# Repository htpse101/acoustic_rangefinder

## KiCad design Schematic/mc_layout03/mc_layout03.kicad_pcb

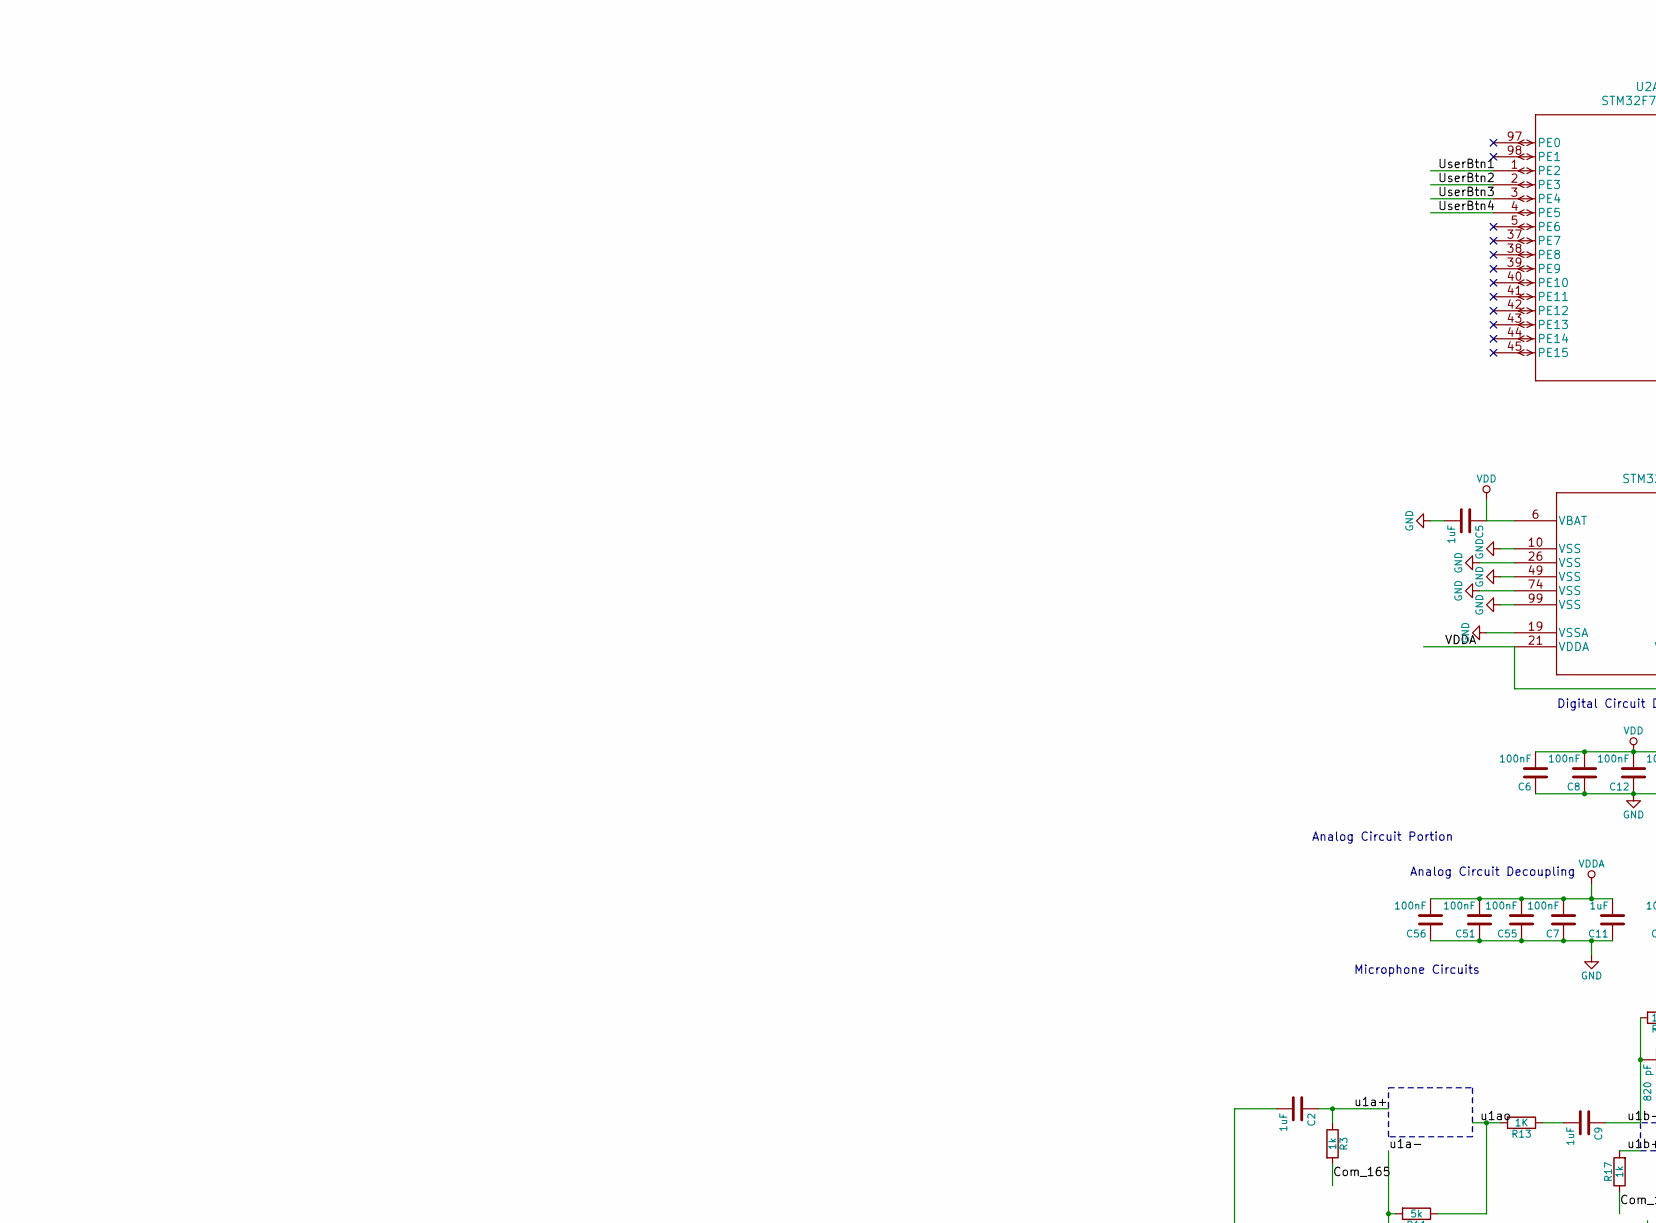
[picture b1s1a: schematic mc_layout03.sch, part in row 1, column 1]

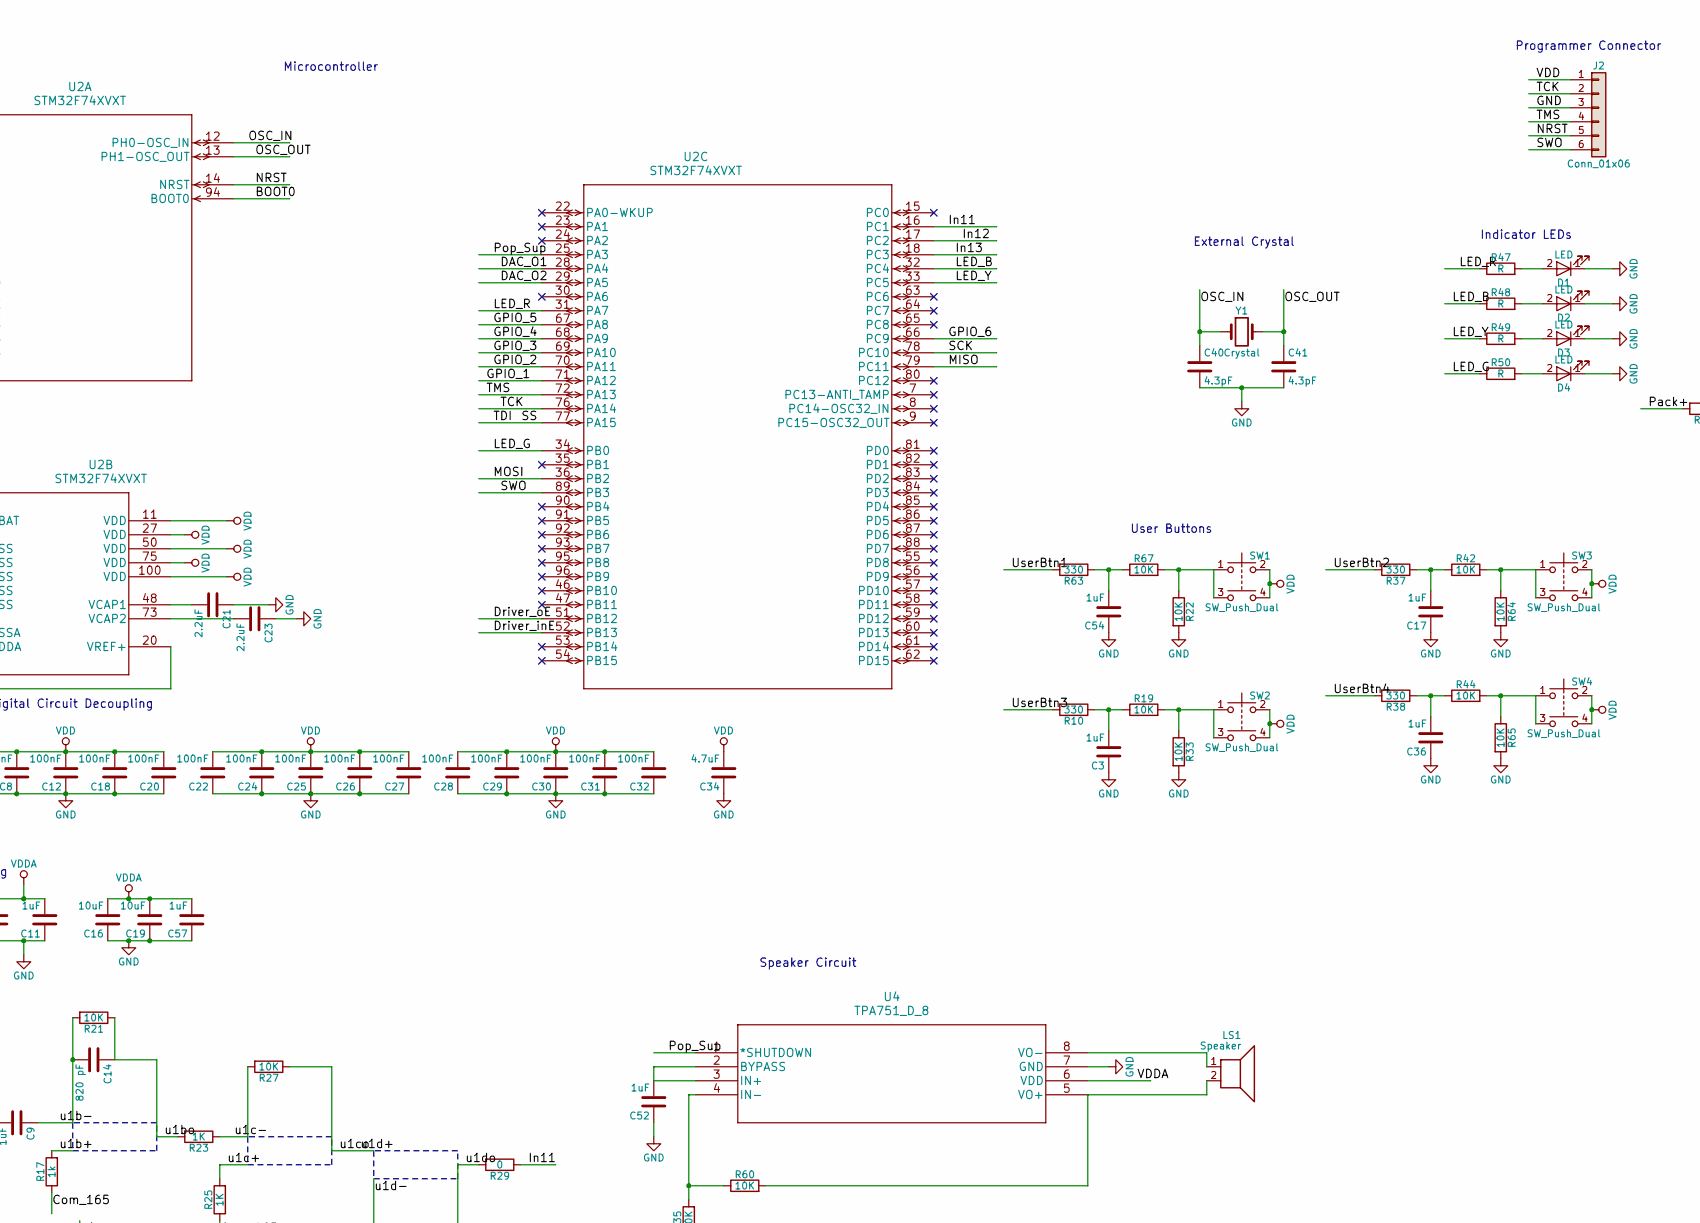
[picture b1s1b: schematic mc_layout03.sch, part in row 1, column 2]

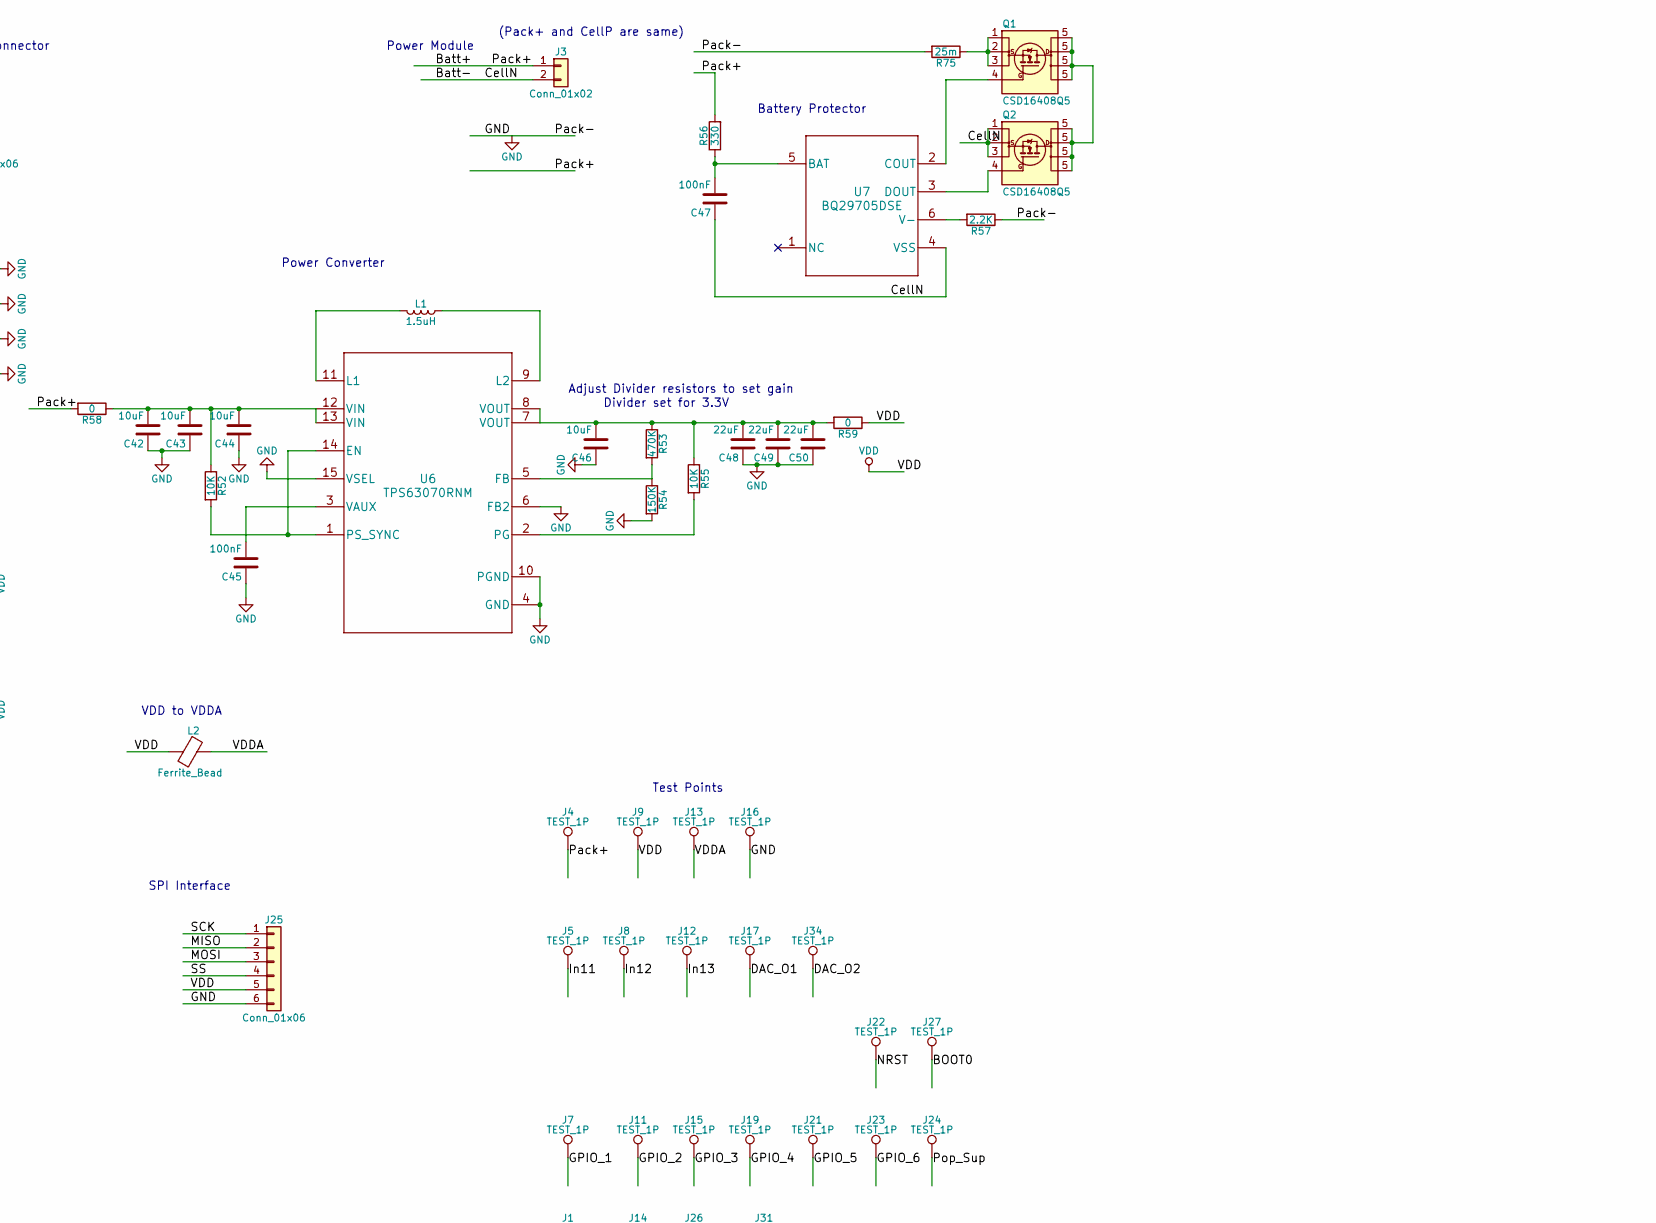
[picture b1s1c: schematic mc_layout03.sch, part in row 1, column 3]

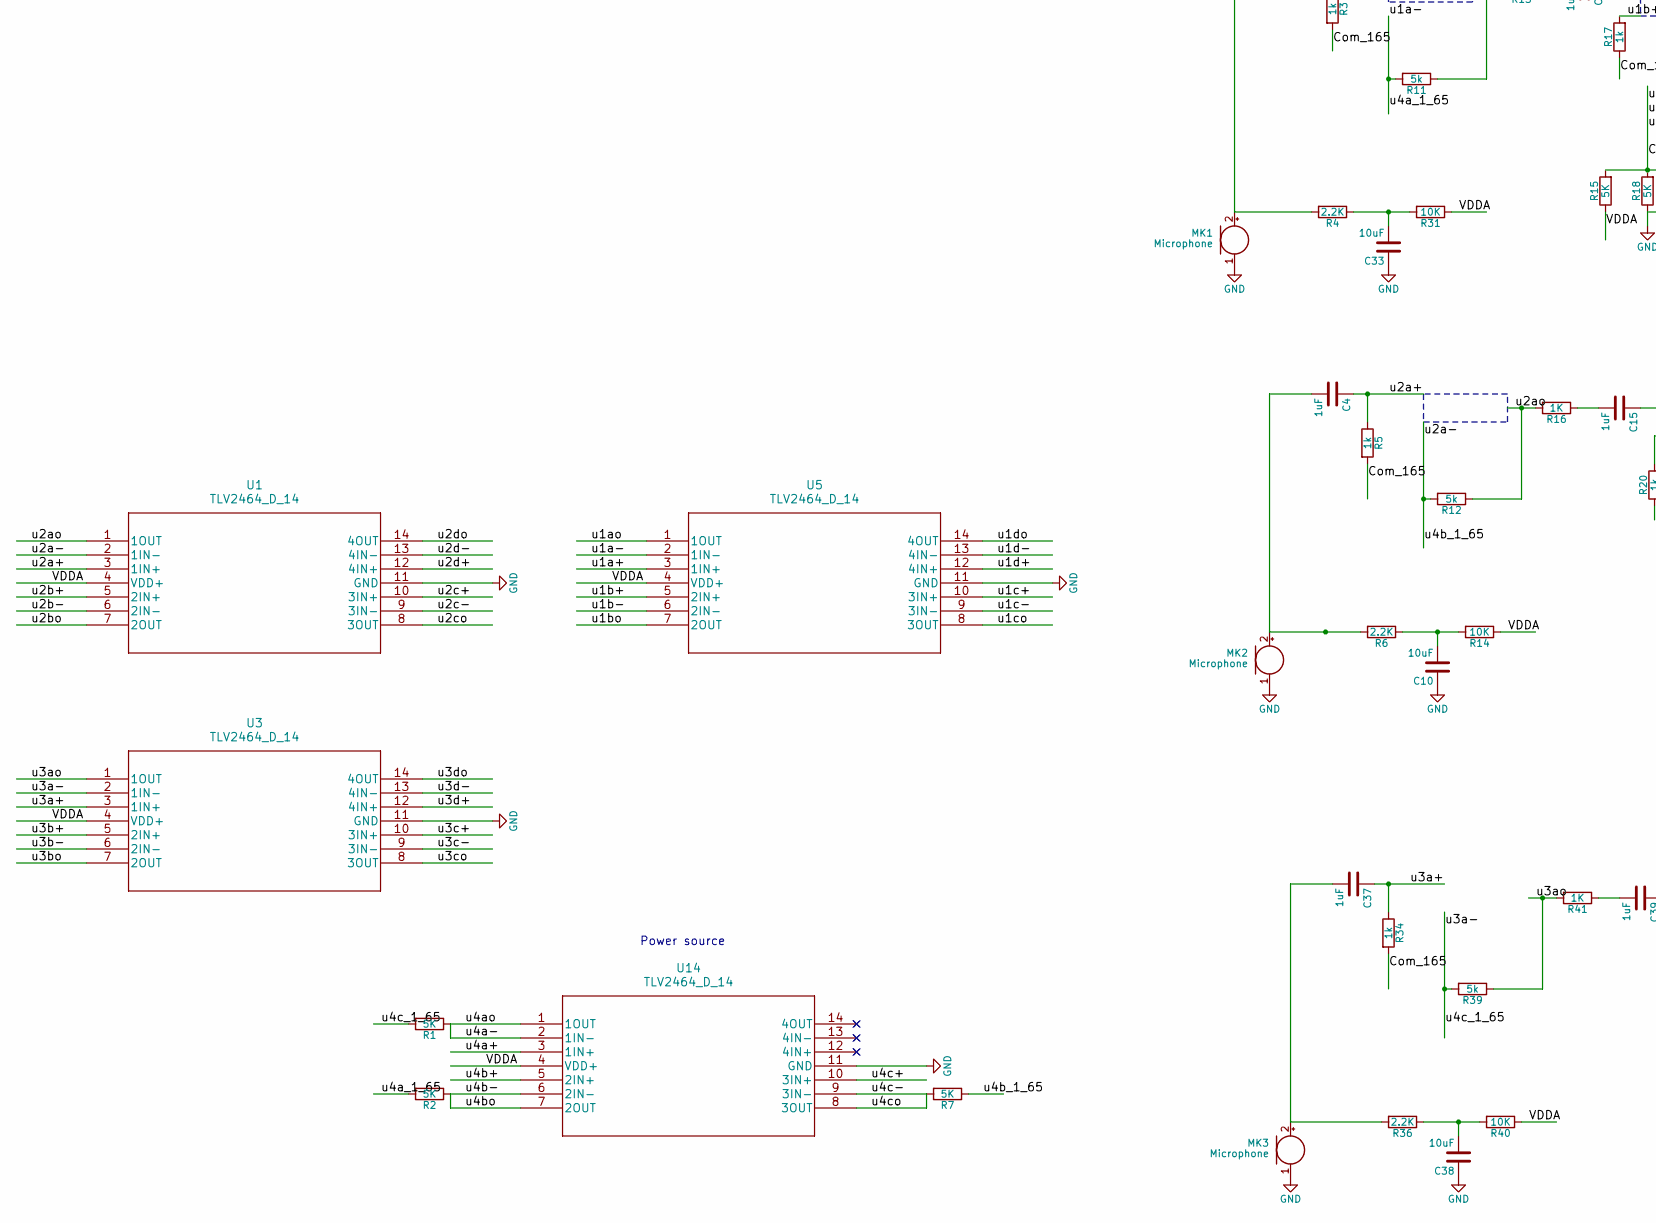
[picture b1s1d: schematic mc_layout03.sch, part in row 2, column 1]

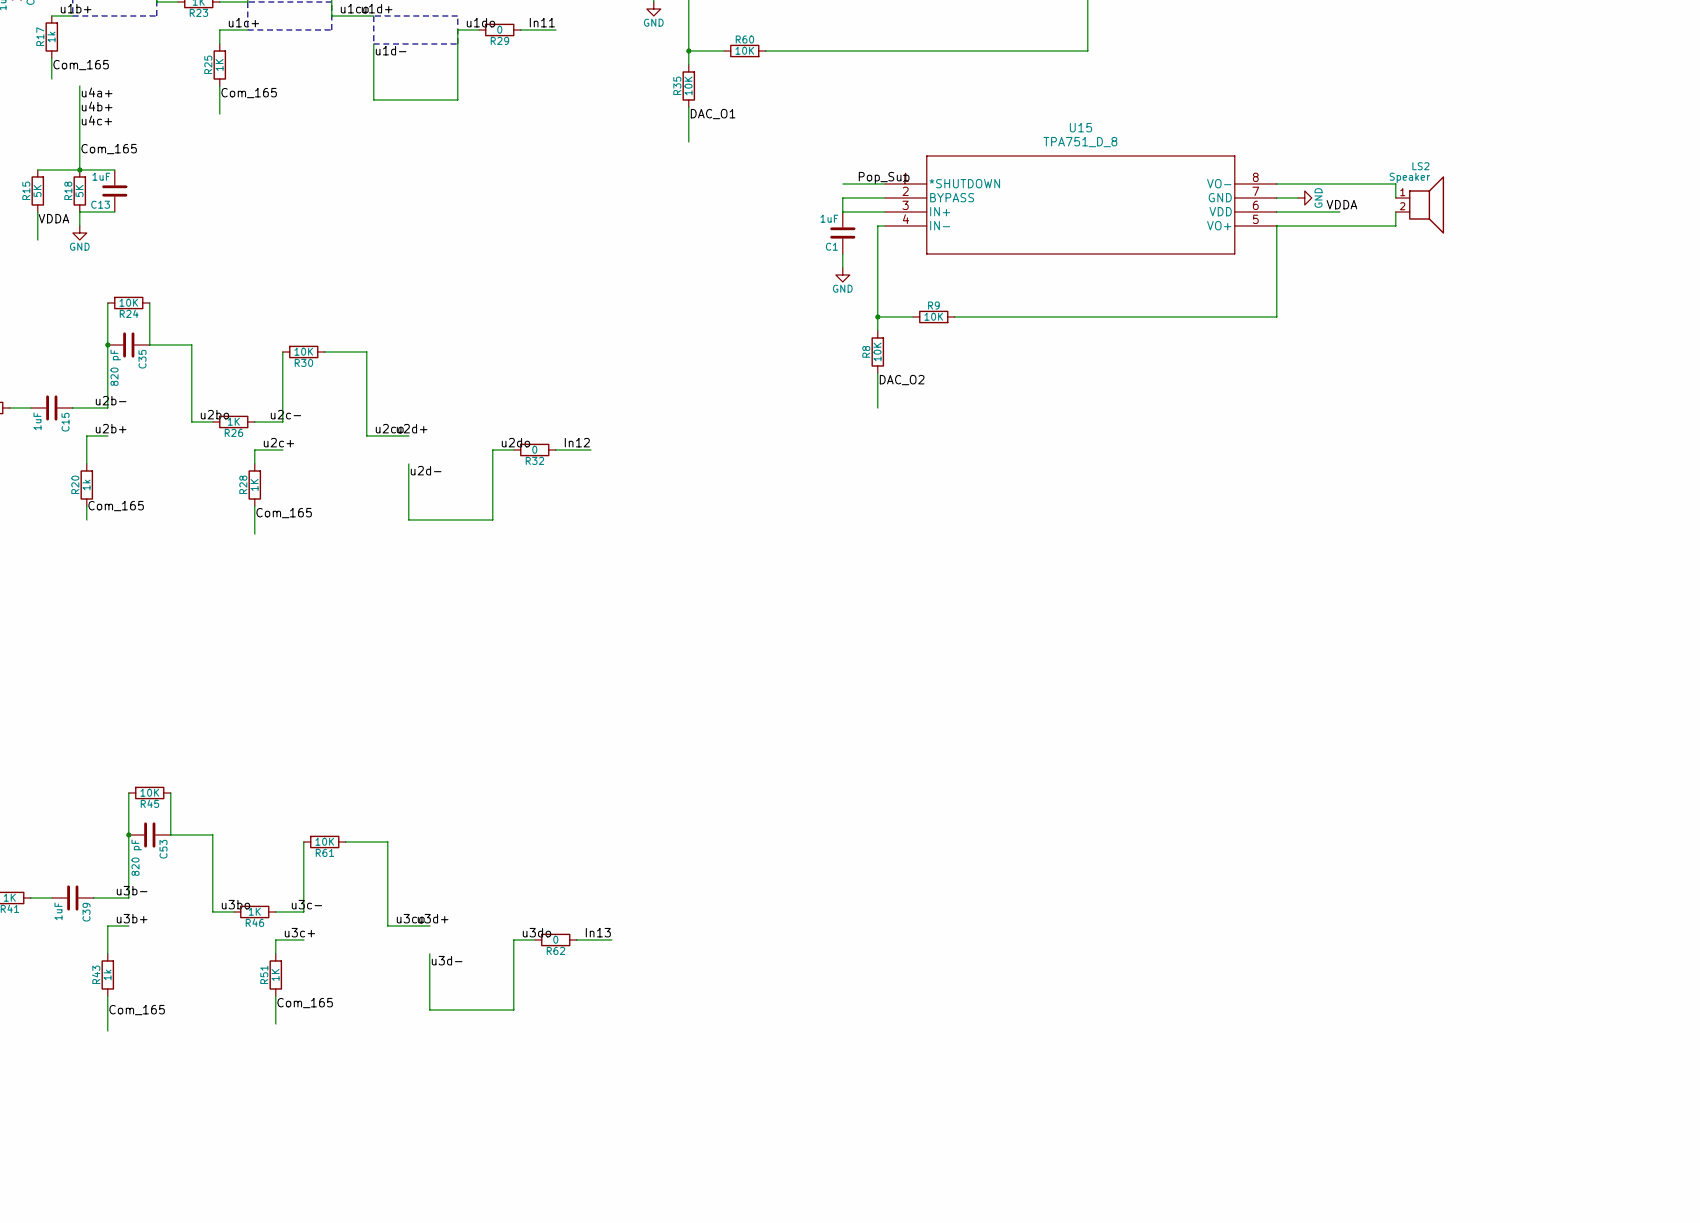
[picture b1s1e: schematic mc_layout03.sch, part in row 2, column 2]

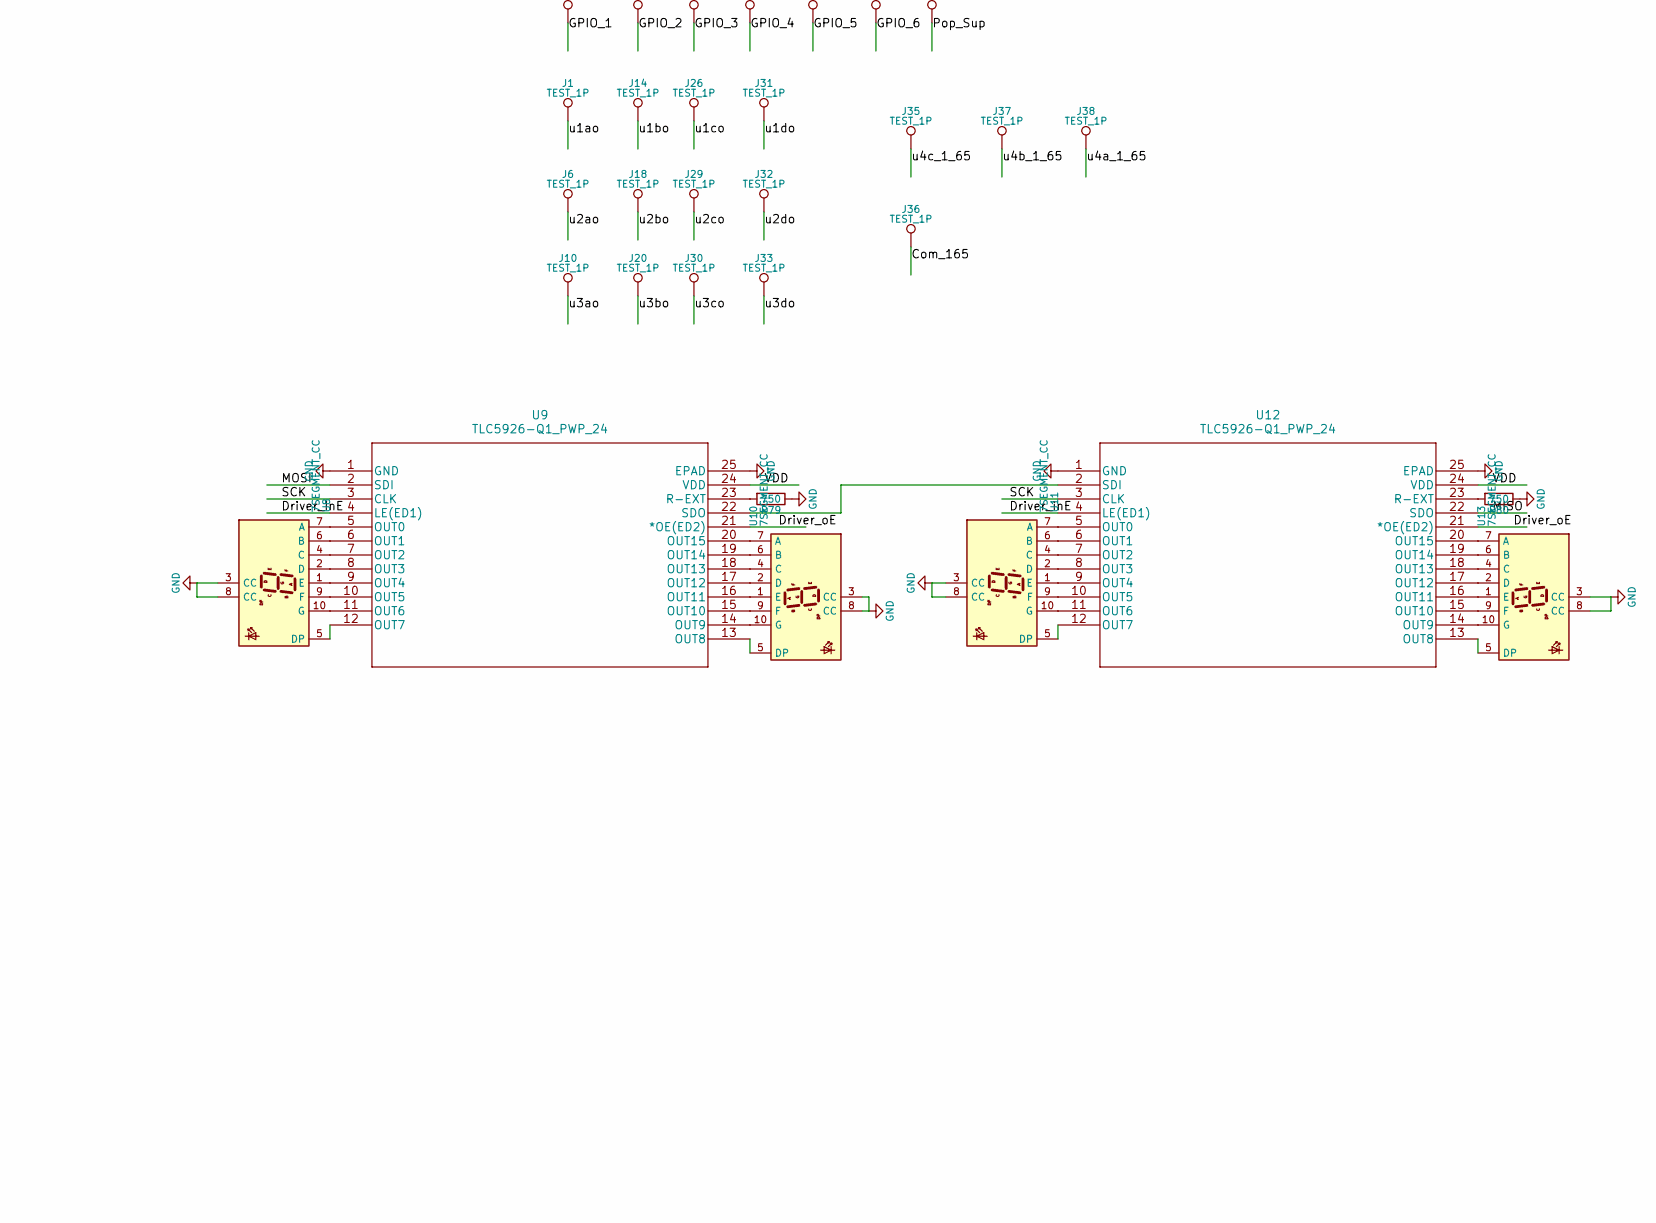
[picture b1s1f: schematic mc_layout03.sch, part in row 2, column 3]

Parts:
C1, C2, C3, C4, C5, C9, C11, C13, C15, C17, C36, C37, C39, C52, C54, C57: 1uF; C_0603
C6, C7, C8, C12, C18, C20, C22, C24, C25, C26, C27, C28, C29, C30, C31, C32, C47, C51, C55, C56: 100nF; C_0603
C10, C16, C19, C33, C38, C44, C46: 10uF; C_0603
C14, C35, C53: 820 pF; C_0603
C21, C23: 2.2uF; C_0603
C34: 4.7uF; C_0603
C40, C41: 4.3pF; C_0603
C42, C43: 10uF; C_0805
C45: 100nF; C_0402
C48, C49, C50: 22uF; C_0805
D1, D2, D3, D4: LED; LED_0603
J1, J4, J5, J6, J8, J9, J10, J12, J13, J14, J16, J17, J18, J20, J22, J24, J26, J27, J29, J30, J31, J32, J33, J34, J35, J36, J37, J38: TEST_1P; TestPt
J2, J25: Conn_01x06; Pin_Header_Straight_1x06_Pitch2.54mm
J3: Conn_01x02; Pin_Header_Straight_1x02_Pitch2.54mm
J7, J11, J15, J19, J21, J23: TEST_1P; LongTestPt
L1: 1.5uH; L_cust01
L2: Ferrite_Bead; L_0603
LS1, LS2: Speaker; Test_Point_2Pads
MK1, MK2, MK3: Microphone; CMC2242PBL
Q1, Q2: CSD16408Q5; CSD16406Q3
R1, R2, R7, R15, R18: 5K; R_0603
R3, R5, R17, R20, R34, R43: 1k; R_0603
R4, R6, R36, R57: 2.2K; R_0603
R8, R9, R14, R19, R21, R22, R24, R27, R30, R31, R33, R35, R40, R42, R44, R45, R52, R55, R60, R61, R64, R65, R67: 10K; R_0603
R10, R37, R38, R56, R63: 330; R_0603
R11, R12, R39: 5k; R_0603
R13, R16, R23, R25, R26, R28, R41, R46, R51: 1K; R_0603
R29, R32, R58, R59, R62: 0; R_0603
R47, R48, R49, R50: R; R_0603
R53: 470K; R_0603
R54: 150K; R_0603
R75: 25m; R_0603
R79, R80: 750; R_0603
SW1, SW2, SW3, SW4: SW_Push_Dual; ADTSM6
U1, U3, U5, U14: TLV2464_D_14
U2: STM32F74XVXT
U4, U15: TPA751_D_8
U6: TPS63070RNM; TPS63070RNMR
U7: BQ29705DSE; BQ29705DSER
U8, U10, U11, U13: 7SEGMENT_CC; INND-SS30
U9, U12: TLC5926-Q1_PWP_24
Y1: Crystal; NX3225GD

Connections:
/BOOT0: J27.1, U2.94 (BOOT0)
/Batt+: J3.1, J4.1, R56.2, R58.2
/Batt-: C47.1, J3.2, Q2.1 (S), Q2.2 (S), Q2.3 (S), U7.4 (VSS)
/Com_165: C13.2, J36.1, R3.2, R5.2, R15.2, R17.1, R18.2, R20.1, R25.1, R28.1, R34.2, R43.1, R51.1, U14.3 (1IN+), U14.5 (2IN+), U14.10 (3IN+)
/DAC_O1: J17.1, R35.1, U2.28 (PA4)
/DAC_O2: J34.1, R8.1, U2.29 (PA5)
/Driver_inE: U2.52 (PB13), U9.4 (LE(ED1)), U12.4 (LE(ED1))
/Driver_oE: U2.51 (PB12), U9.21 (*OE(ED2)), U12.21 (*OE(ED2))
/GPIO_1: J7.1, U2.71 (PA12)
/GPIO_2: J11.1, U2.70 (PA11)
/GPIO_3: J15.1, U2.69 (PA10)
/GPIO_4: J19.1, U2.68 (PA9)
/GPIO_5: J21.1, U2.67 (PA8)
/GPIO_6: J23.1, U2.66 (PC9)
/In11: J5.1, R29.1, U2.16 (PC1)
/In12: J8.1, R32.1, U2.17 (PC2)
/In13: J12.1, R62.1, U2.18 (PC3)
/LED_B: R48.1, U2.32 (PC4)
/LED_G: R50.1, U2.34 (PB0)
/LED_R: R47.1, U2.31 (PA7)
/LED_Y: R49.1, U2.33 (PC5)
/MISO: J25.2, U2.79 (PC11), U12.22 (SDO)
/MOSI: J25.3, U2.36 (PB2), U9.2 (SDI)
/NRST: J2.5, J22.1, U2.14 (NRST)
/OSC_IN: C40.1, U2.12 (PH0-OSC_IN), Y1.1
/OSC_OUT: C41.1, U2.13 (PH1-OSC_OUT), Y1.2
/Pop_Sup: J24.1, U2.25 (PA3), U4.1 (*SHUTDOWN), U15.1 (*SHUTDOWN)
/SCK: J25.1, U2.78 (PC10), U9.3 (CLK), U12.3 (CLK)
/SS: J25.4, U2.77 (PA15); also elsewhere on the board
/SWO: J2.6, U2.89 (PB3)
/TCK: J2.2, U2.76 (PA14)
/TMS: J2.4, U2.72 (PA13)
/UserBtn1: R63.2, U2.1 (PE2)
/UserBtn2: R37.2, U2.2 (PE3)
/UserBtn3: R10.2, U2.3 (PE4)
/UserBtn4: R38.2, U2.4 (PE5)
/u1a+: C2.1, R3.1, U5.3 (1IN+)
/u1a-: J38.1, R2.2, R11.2, U5.2 (1IN-)
/u1ao: J1.1, R11.1, R13.2, U5.1 (1OUT)
/u1b+: R17.2, U5.5 (2IN+)
/u1b-: C9.1, C14.2, R21.2, U5.6 (2IN-)
/u1bo: C14.1, J14.1, R21.1, R23.2, U5.7 (2OUT)
/u1c+: R25.2, U5.10 (3IN+)
/u1c-: R23.1, R27.2, U5.9 (3IN-)
/u1co: J26.1, R27.1, U5.8 (3OUT), U5.12 (4IN+)
/u1d-: J31.1, R29.2, U5.13 (4IN-), U5.14 (4OUT)
/u2a+: C4.1, R5.1, U1.3 (1IN+)
/u2a-: J37.1, R7.1, R12.2, U1.2 (1IN-)
/u2ao: J6.1, R12.1, R16.2, U1.1 (1OUT)
/u2b+: R20.2, U1.5 (2IN+)
/u2b-: C15.1, C35.2, R24.2, U1.6 (2IN-)
/u2bo: C35.1, J18.1, R24.1, R26.2, U1.7 (2OUT)
/u2c+: R28.2, U1.10 (3IN+)
/u2c-: R26.1, R30.2, U1.9 (3IN-)
/u2co: J29.1, R30.1, U1.8 (3OUT), U1.12 (4IN+)
/u2d-: J32.1, R32.2, U1.13 (4IN-), U1.14 (4OUT)
/u3a+: C37.1, R34.1, U3.3 (1IN+)
/u3a-: J35.1, R1.2, R39.2, U3.2 (1IN-)
/u3ao: J10.1, R39.1, R41.2, U3.1 (1OUT)
/u3b+: R43.2, U3.5 (2IN+)
/u3b-: C39.1, C53.2, R45.2, U3.6 (2IN-)
/u3bo: C53.1, J20.1, R45.1, R46.2, U3.7 (2OUT)
/u3c+: R51.2, U3.10 (3IN+)
/u3c-: R46.1, R61.2, U3.9 (3IN-)
/u3co: J30.1, R61.1, U3.8 (3OUT), U3.12 (4IN+)
/u3d-: J33.1, R62.2, U3.13 (4IN-), U3.14 (4OUT)
/u4a-: R1.1, U14.1 (1OUT), U14.2 (1IN-)
/u4b-: R2.1, U14.6 (2IN-), U14.7 (2OUT)
/u4c-: R7.2, U14.8 (3OUT), U14.9 (3IN-)
GND: C1.1, C3.1, C5.2, C6.1, C7.1, C8.1, C10.1, C11.1, C12.1, C13.1, C16.1, C17.1, C18.1, C19.1, C20.1, C21.1, C22.1, C23.1, C24.1, C25.1, C26.1, C27.1, C28.1, C29.1, C30.1, C31.1, C32.1, C33.1, C34.1, C36.1, C38.1, C40.2, C41.2, C42.1, C43.1, C44.1, C45.1, C46.1, C48.1, C49.1, C50.1, C51.1, C52.1, C54.1, C55.1, C56.1, C57.1, D1.1 (K), D2.1 (K), D3.1 (K), D4.1 (K), J2.3, J16.1, J25.6, MK1.1 (-), MK2.1 (-), MK3.1 (-), R18.1, R22.2, R33.2, R54.2, R57.1, R64.2, R65.2, R75.2, R79.1, R80.1, U1.11 (GND), U2.10 (VSS), U2.19 (VSSA), U2.26 (VSS), U2.49 (VSS), U2.74 (VSS), U2.99 (VSS), U3.11 (GND), U4.7 (GND), U5.11 (GND), U6.4 (GND), U6.6 (FB2), U6.10 (PGND), U6.15 (VSEL), U8.3 (CC), U8.8 (CC), U9.1 (GND), U9.25 (EPAD), U10.3 (CC), U10.8 (CC), U11.3 (CC), U11.8 (CC), U12.1 (GND), U12.25 (EPAD), U13.3 (CC), U13.8 (CC), U14.11 (GND), U15.7 (GND)
unnamed: C1.2, U15.2 (BYPASS), U15.3 (IN+)
unnamed: C2.2, MK1.2 (+), R4.2
unnamed: C3.2, R10.1, R19.1
unnamed: C4.2, MK2.2 (+), R6.2
unnamed: C9.2, R13.1
unnamed: C10.2, R6.1, R14.2
unnamed: C15.2, R16.1
unnamed: C17.2, R37.1, R42.1
unnamed: C21.2, U2.48 (VCAP1)
unnamed: C23.2, U2.73 (VCAP2)
unnamed: C33.2, R4.1, R31.2
unnamed: C36.2, R38.1, R44.1
unnamed: C37.2, MK3.2 (+), R36.2
unnamed: C38.2, R36.1, R40.2
unnamed: C39.2, R41.1
unnamed: C42.2, C43.2, C44.2, R52.1, R58.1, U6.12 (VIN), U6.13 (VIN)
unnamed: C45.2, U6.3 (VAUX)
unnamed: C46.2, C48.2, C49.2, C50.2, R53.1, R55.1, R59.2, U6.7 (VOUT), U6.8 (VOUT)
unnamed: C47.2, R56.1, U7.5 (BAT)
unnamed: C52.2, U4.2 (BYPASS), U4.3 (IN+)
unnamed: C54.2, R63.1, R67.1
unnamed: D1.2 (A), R47.2
unnamed: D2.2 (A), R48.2
unnamed: D3.2 (A), R49.2
unnamed: D4.2 (A), R50.2
unnamed: L1.1, U6.9 (L2)
unnamed: L1.2, U6.11 (L1)
unnamed: LS1.1, U4.8 (VO-)
unnamed: LS1.2, R60.2, U4.5 (VO+)
unnamed: LS2.1, U15.8 (VO-)
unnamed: LS2.2, R9.2, U15.5 (VO+)
unnamed: Q1.1 (S), Q1.2 (S), Q1.3 (S), R75.1
unnamed: Q1.4 (G), U7.2 (COUT)
unnamed: Q1.5 (D), Q2.5 (D)
unnamed: Q2.4 (G), U7.3 (DOUT)
unnamed: R8.2, R9.1, U15.4 (IN-)
unnamed: R19.2, R33.1, SW2.1, SW2.3
unnamed: R22.1, R67.2, SW1.1, SW1.3
unnamed: R35.2, R60.1, U4.4 (IN-)
unnamed: R42.2, R64.1, SW3.1, SW3.3
unnamed: R44.2, R65.1, SW4.1, SW4.3
unnamed: R52.2, U6.1 (PS_SYNC), U6.14 (EN)
unnamed: R53.2, R54.1, U6.5 (FB)
unnamed: R55.2, U6.2 (PG)
unnamed: R57.2, U7.6 (V-)
unnamed: R79.2, U9.23 (R-EXT)
unnamed: R80.2, U12.23 (R-EXT)
unnamed: U8.1 (E), U9.9 (OUT4)
unnamed: U8.2 (D), U9.8 (OUT3)
unnamed: U8.4 (C), U9.7 (OUT2)
unnamed: U8.5 (DP), U9.12 (OUT7)
unnamed: U8.6 (B), U9.6 (OUT1)
unnamed: U8.7 (A), U9.5 (OUT0)
unnamed: U8.9 (F), U9.10 (OUT5)
unnamed: U8.10 (G), U9.11 (OUT6)
unnamed: U9.16 (OUT11), U10.1 (E)
unnamed: U9.17 (OUT12), U10.2 (D)
unnamed: U9.18 (OUT13), U10.4 (C)
unnamed: U9.13 (OUT8), U10.5 (DP)
unnamed: U9.19 (OUT14), U10.6 (B)
unnamed: U9.20 (OUT15), U10.7 (A)
unnamed: U9.15 (OUT10), U10.9 (F)
unnamed: U9.14 (OUT9), U10.10 (G)
unnamed: U11.1 (E), U12.9 (OUT4)
unnamed: U11.2 (D), U12.8 (OUT3)
unnamed: U11.4 (C), U12.7 (OUT2)
unnamed: U11.5 (DP), U12.12 (OUT7)
unnamed: U11.6 (B), U12.6 (OUT1)
unnamed: U11.7 (A), U12.5 (OUT0)
unnamed: U11.9 (F), U12.10 (OUT5)
unnamed: U11.10 (G), U12.11 (OUT6)
unnamed: U9.22 (SDO), U12.2 (SDI)
unnamed: U12.13 (OUT8), U13.5 (DP)
unnamed: U12.14 (OUT9), U13.10 (G)
unnamed: U12.15 (OUT10), U13.9 (F)
unnamed: U12.16 (OUT11), U13.1 (E)
unnamed: U12.17 (OUT12), U13.2 (D)
unnamed: U12.18 (OUT13), U13.4 (C)
unnamed: U12.19 (OUT14), U13.6 (B)
unnamed: U12.20 (OUT15), U13.7 (A)
VDD: C5.1, C6.2, C8.2, C12.2, C18.2, C20.2, C22.2, C24.2, C25.2, C26.2, C27.2, C28.2, C29.2, C30.2, C31.2, C32.2, C34.2, J2.1, J9.1, J25.5, L2.2, R59.1, SW1.2, SW1.4, SW2.2, SW2.4, SW3.2, SW3.4, SW4.2, SW4.4, U2.6 (VBAT), U2.11 (VDD), U2.27 (VDD), U2.50 (VDD), U2.75 (VDD), U2.100 (VDD), U9.24 (VDD), U12.24 (VDD)
VDDA: C7.2, C11.2, C16.2, C19.2, C51.2, C55.2, C56.2, C57.2, J13.1, L2.1, R14.1, R15.1, R31.1, R40.1, U1.4 (VDD+), U2.20 (VREF+), U2.21 (VDDA), U3.4 (VDD+), U4.6 (VDD), U5.4 (VDD+), U14.4 (VDD+), U15.6 (VDD)

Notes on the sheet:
Microcontroller
Microphone Circuits
Speaker Circuit
Programmer Connector
Power Module
External Crystal
Indicator LEDs
Battery Protector
Power Converter
Adjust Divider resistors to set gain
Divider set for 3.3V
(Pack+ and CellP are same)
Analog Circuit Portion
Digital Circuit Decoupling
Analog Circuit Decoupling
Test Points
User Buttons
VDD to VDDA
SPI Interface
Power source

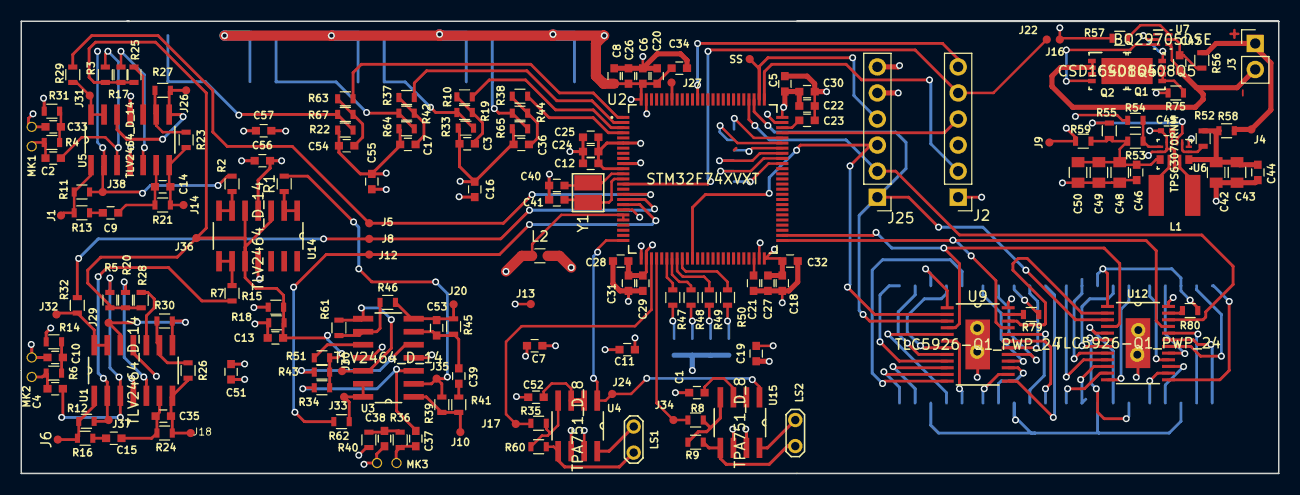
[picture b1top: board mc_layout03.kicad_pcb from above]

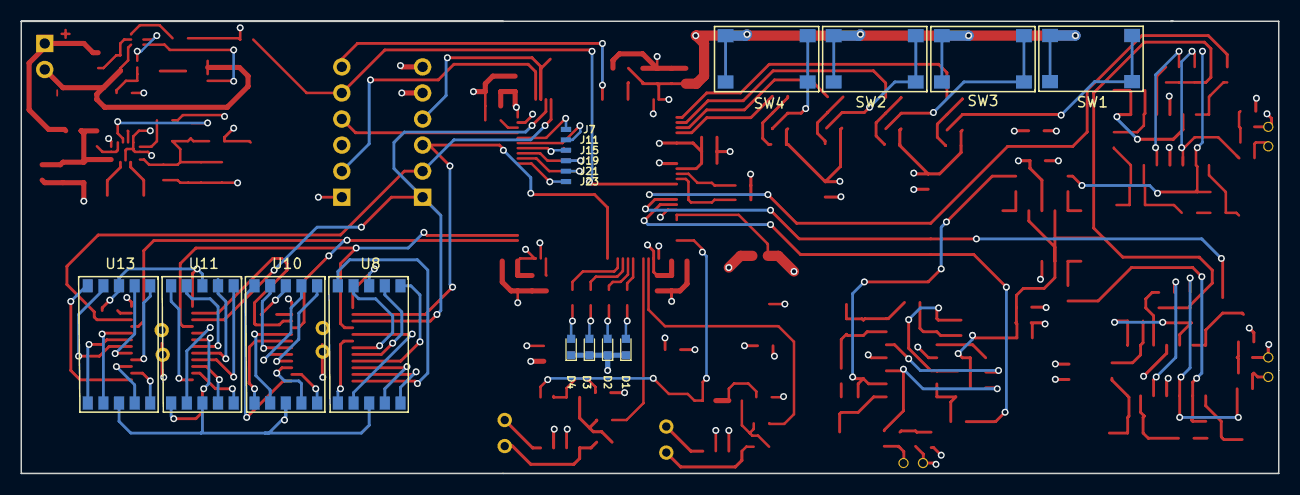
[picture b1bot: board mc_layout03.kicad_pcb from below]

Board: 4 copper layers, 122.6 x 44.1 mm, 197 parts (18 on the bottom side), 152 nets.

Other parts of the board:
SS: TEST_1P; TestPt

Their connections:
/SS: SS.1; also elsewhere on the board

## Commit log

2018-02-17 Feature #1 Initial commit of project code base.
2018-02-19 #1 Added MatLab code. mc_interface.m will save data to a file that the MC will load. The MC will save data into a file that the mc_interface.m will load. Toggle this with the 'if' block in the mc_int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
2018-02-19 #2 This is the reverted version. Before it was committed, it was verified that it successfully made a distance measurement by accessing both the ADC and DAC. This code is not in a broken state. It co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
2018-02-19 #1 Added documentation files. These were helpful for setting up the project. Most of them were gathered from the STM website.
2018-02-19 #1 Lightened the Calculations.xlsx file by a lot.
2018-03-10 Issue #3 These files are the schematic.
2018-03-10 Issue #1 Updated the Calculations.xlsx file. It now has details about the schematic layout and some of the registers for troubleshooting the DMA and ADC issues.
2018-03-13 Issue #1 This code has updates to allow more functionality with sampling off several pins sequentially.
2018-03-13 Issue #1 Updated the project files to make them much cleaner. The DAC does not currently run properly. The timers are also off and need to be re-scaled.
2018-03-13 Added cor and cov with float
2018-03-13 Test code for conv in matlab.

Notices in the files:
parts and their libraries:
Copyright 2016 Accelerated Designs. All rights reserved.
